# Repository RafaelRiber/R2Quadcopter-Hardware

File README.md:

# R2Quadcopter-Hardware

# Description

The R<sup>2</sup>Quad is an ARM Cortex M0+ Processor-Based radio controlled quadcopter flight controller.

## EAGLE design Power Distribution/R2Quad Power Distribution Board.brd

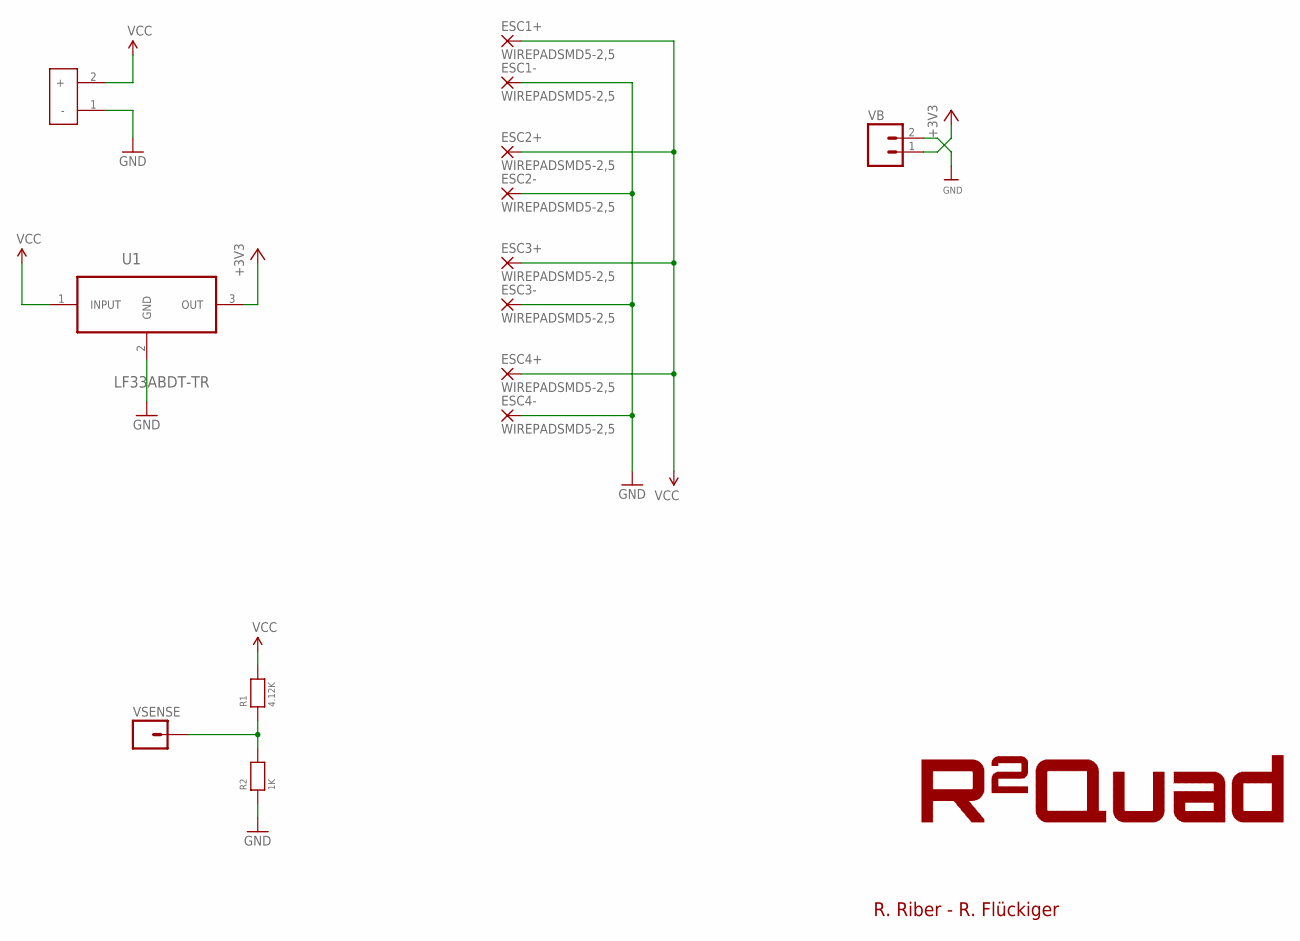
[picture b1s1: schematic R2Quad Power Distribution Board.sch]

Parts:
ESC1+, ESC1-, ESC2+, ESC2-, ESC3+, ESC3-, ESC4+, ESC4-: WIREPADSMD5-2,5; 5-2,5
R1: 4.12K; 0603
R2: 1K; 0603
U1: LF33ABDT-TR; TO228P972X240-3N
U$1: XT60
VB: M02PTH; 1X02
VSENSE: M01PTH; 1X01

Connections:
+3V3: U1.3 (OUT), VB.1
GND: ESC1-.1, ESC2-.1, ESC3-.1, ESC4-.1, R2.1, U1.2 (GND), U$1.1 (-), VB.2
unnamed: R1.1, R2.2, VSENSE.1
VCC: ESC1+.1, ESC2+.1, ESC3+.1, ESC4+.1, R1.2, U1.1 (INPUT), U$1.2 (+)

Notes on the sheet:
R. Riber - R. Flückiger

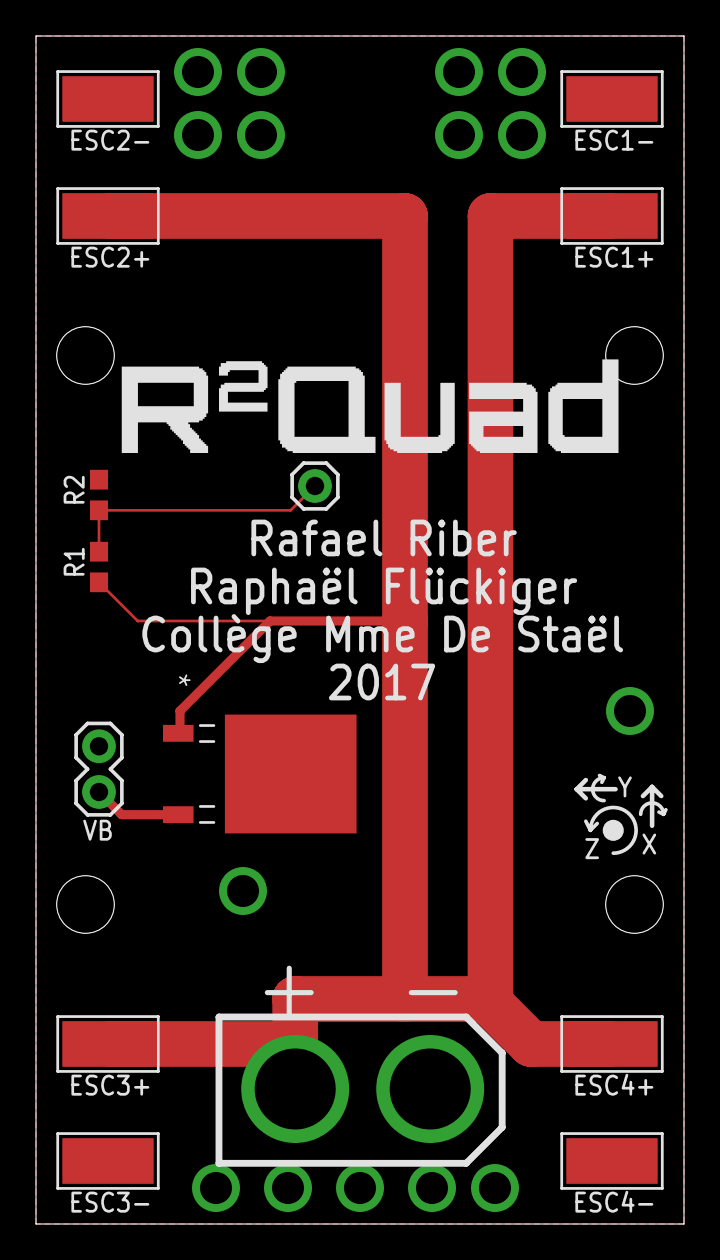
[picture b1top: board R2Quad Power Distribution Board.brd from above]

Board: 2 copper layers, 36.0 x 66.0 mm, 16 parts (0 on the bottom side), 4 nets.

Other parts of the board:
U$2: R2QUAD_LOGO
U$3: SENSOR_AXIS

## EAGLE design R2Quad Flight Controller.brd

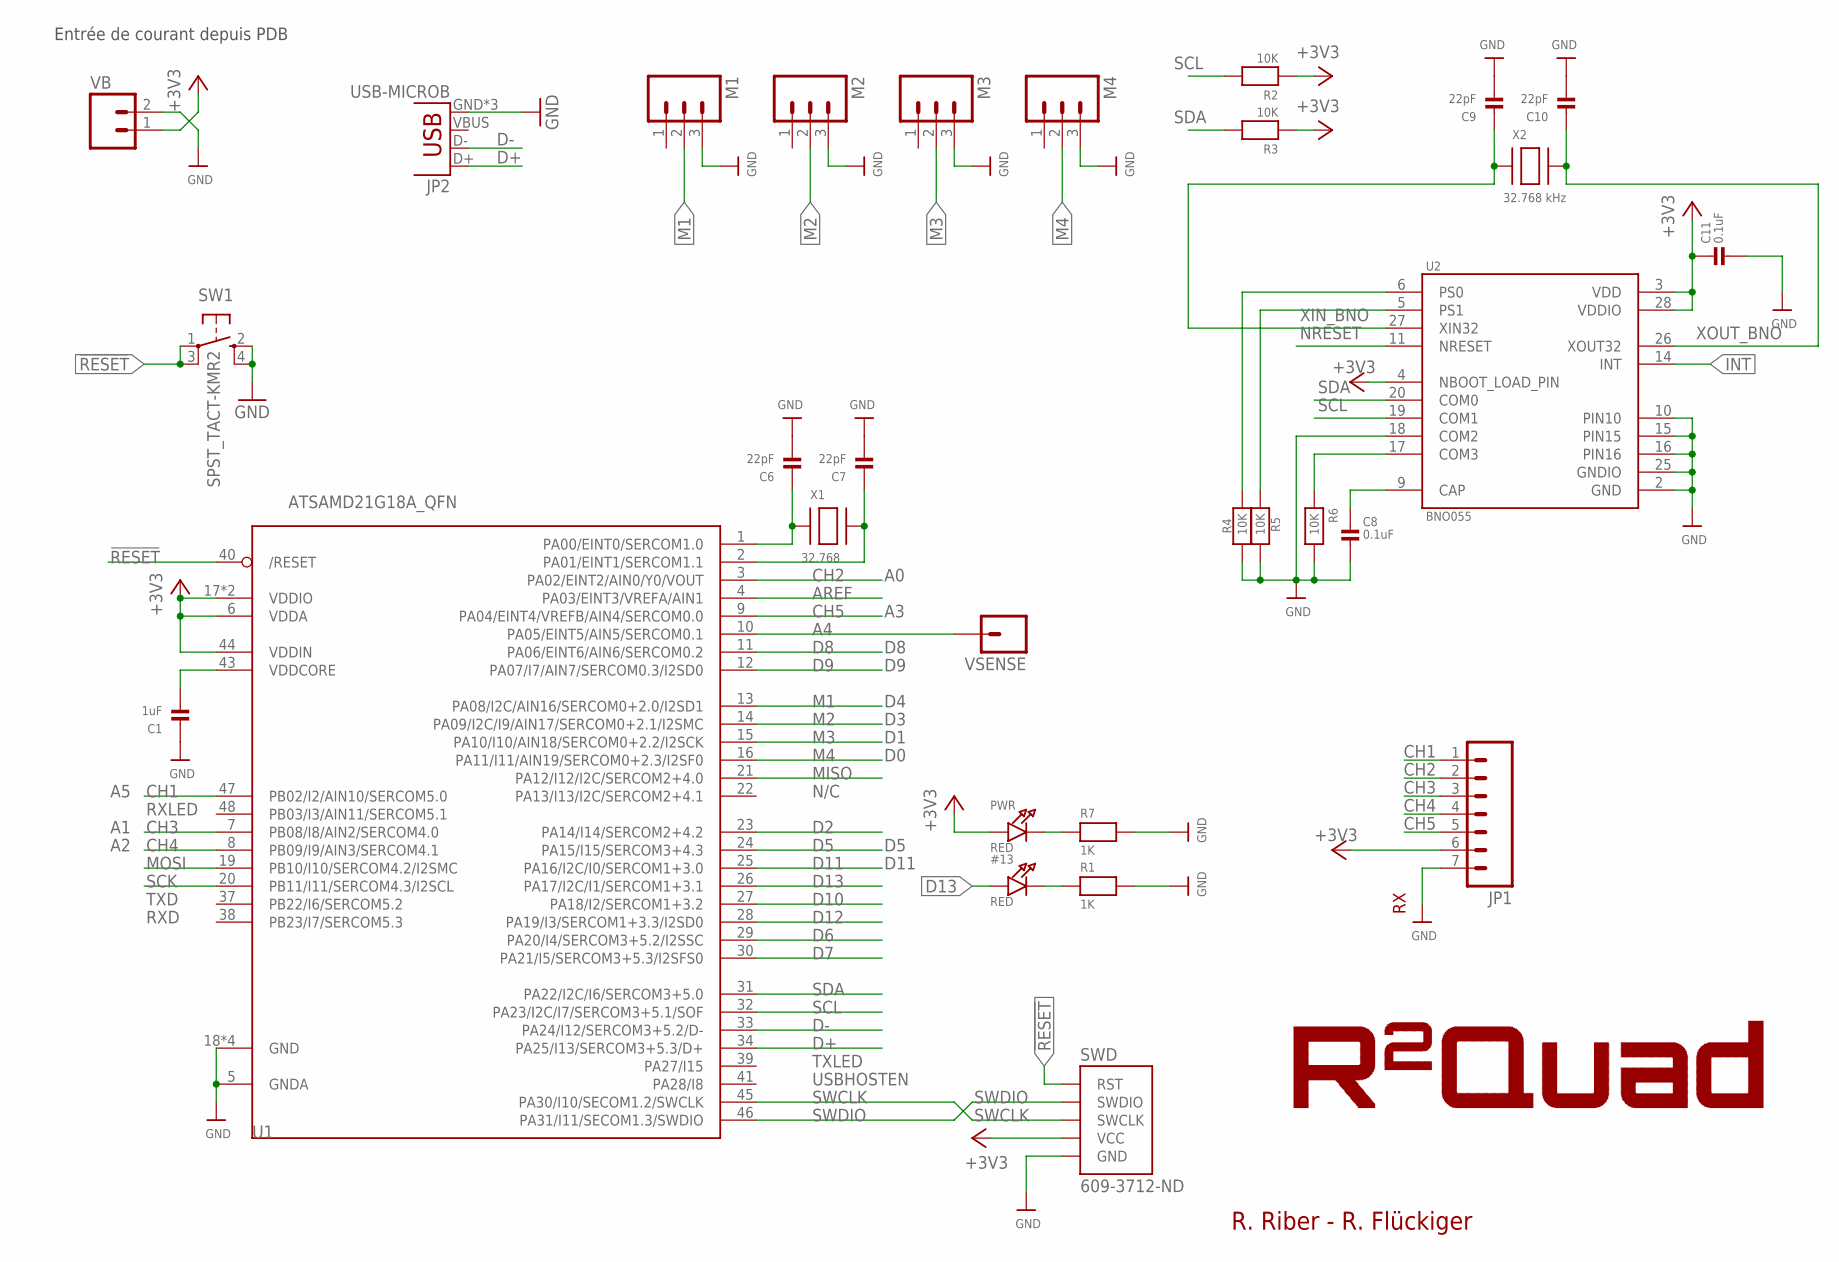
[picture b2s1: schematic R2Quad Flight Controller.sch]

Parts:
#13: RED; CHIPLED_0805; MPN LGQ971
C1: 1uF; 0603
C6, C7, C9, C10: 22pF; 0603
C8, C11: 0.1uF; 0603
JP1: M07; 1X07
JP2: USB-MICROB; MPN 10104110-0001LF
M1, M2, M3, M4: M03PTH; 1X03
PWR: RED; CHIPLED_0805; MPN LGQ971
R1, R7: 1K; 0603; MPN CRCW06032K20JNEA
R2, R3, R4, R5, R6: 10K; 0603; MPN CRCW060310K0FKEA
SW1: SPST_TACT-KMR2; KMR2
SWD: 609-3712-ND; SWD-2X5
U1: ATSAMD21G18A_QFN; TQFN48_7MM
U2: BNO055; LGA28R50P4X10_380X520X100
VB: M02PTH; 1X02
VSENSE: M01PTH; 1X01
X1: 32.768; XTAL3215
X2: 32.768 kHz; XTAL3215

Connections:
!RESET: SW1.1, SW1.3 (P1), SWD.RST, U1.40 (/RESET)
+3V3: C11.2, JP1.6, PWR.A, R2.1, R3.1, SWD.VCC, U1.6 (VDDA), U1.17 (VDDIO), U1.36 (VDDIO), U1.44 (VDDIN), U2.3 (VDD), U2.4 (NBOOT_LOAD_PIN), U2.28 (VDDIO), VB.1
A4: U1.10 (PA05/EINT5/AIN5/SERCOM0.1), VSENSE.1
AREF: U1.4 (PA03/EINT3/VREFA/AIN1)
CH1: JP1.1, U1.47 (PB02/I2/AIN10/SERCOM5.0)
CH2: JP1.2, U1.3 (PA02/EINT2/AIN0/Y0/VOUT)
CH3: JP1.3, U1.7 (PB08/I8/AIN2/SERCOM4.0)
CH4: JP1.4, U1.8 (PB09/I9/AIN3/SERCOM4.1)
CH5: JP1.5, U1.9 (PA04/EINT4/VREFB/AIN4/SERCOM0.0)
D2: U1.23 (PA14/I14/SERCOM2+4.2)
D5: U1.24 (PA15/I15/SERCOM3+4.3)
D6: U1.29 (PA20/I4/SERCOM3+5.2/I2SSC)
D7: U1.30 (PA21/I5/SERCOM3+5.3/I2SFS0)
D8: U1.11 (PA06/EINT6/AIN6/SERCOM0.2)
D9: U1.12 (PA07/I7/AIN7/SERCOM0.3/I2SD0)
D10: U1.27 (PA18/I2/SERCOM1+3.2)
D11: U1.25 (PA16/I2C/I0/SERCOM1+3.0)
D12: U1.28 (PA19/I3/SERCOM1+3.3/I2SD0)
D13: #13.A, U1.26 (PA17/I2C/I1/SERCOM1+3.1)
D+: JP2.D+, U1.34 (PA25/I13/SERCOM3+5.3/D+)
D-: JP2.D-, U1.33 (PA24/I12/SERCOM3+5.2/D-)
GND: C1.1, C6.2, C7.2, C8.1, C9.2, C10.2, C11.1, JP1.7, JP2.GND, JP2.MT1 (GND), JP2.MT2 (GND), M1.3, M2.3, M3.3, M4.3, R1.2, R4.2, R5.2, R6.2, R7.2, SW1.2 (S), SW1.4 (S1), SWD.GND@1 (GND), SWD.GND@2 (GND), SWD.GND@3 (GND), U1.5 (GNDA), U1.18 (GND), U1.35 (GND), U1.42 (GND), U1.THERMAL (GND), U2.2 (GND), U2.10 (PIN10), U2.15 (PIN15), U2.16 (PIN16), U2.18 (COM2), U2.25 (GNDIO), VB.2
INT: U2.14 (INT)
M1: M1.2, U1.13 (PA08/I2C/AIN16/SERCOM0+2.0/I2SD1)
M2: M2.2, U1.14 (PA09/I2C/I9/AIN17/SERCOM0+2.1/I2SMC)
M3: M3.2, U1.15 (PA10/I10/AIN18/SERCOM0+2.2/I2SCK)
M4: M4.2, U1.16 (PA11/I11/AIN19/SERCOM0+2.3/I2SF0)
MISO: U1.21 (PA12/I12/I2C/SERCOM2+4.0)
MOSI: U1.19 (PB10/I10/SERCOM4.2/I2SMC)
unnamed: PWR.C, R7.1
unnamed: C8.2, U2.9 (CAP)
unnamed: R6.1, U2.17 (COM3)
unnamed: R5.1, U2.5 (PS1)
unnamed: R4.1, U2.6 (PS0)
unnamed: C6.1, U1.1 (PA00/EINT0/SERCOM1.0), X1.P$1
unnamed: C7.1, U1.2 (PA01/EINT1/SERCOM1.1), X1.P$2
unnamed: #13.C, R1.1
NRESET: U2.11 (NRESET)
SCK: U1.20 (PB11/I11/SERCOM4.3/I2SCL)
SCL: R2.2, U1.32 (PA23/I2C/I7/SERCOM3+5.1/SOF), U2.19 (COM1)
SDA: R3.2, U1.31 (PA22/I2C/I6/SERCOM3+5.0), U2.20 (COM0)
SWCLK: SWD.SWCLK, U1.45 (PA30/I10/SECOM1.2/SWCLK)
SWDIO: SWD.SWDIO, U1.46 (PA31/I11/SECOM1.3/SWDIO)
VDDCORE1: C1.2, U1.43 (VDDCORE)
XIN_BNO: C9.1, U2.27 (XIN32), X2.P$1
XOUT_BNO: C10.1, U2.26 (XOUT32), X2.P$2

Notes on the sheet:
N/C
TXLED
USBHOSTEN
RXLED
TXD
RXD
D11
R. Riber - R. Flückiger
Entrée de courant depuis PDB

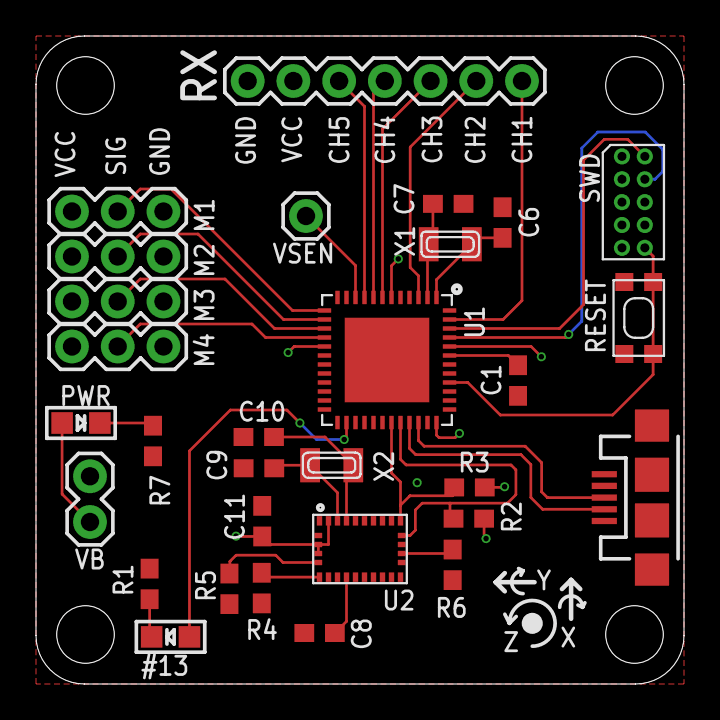
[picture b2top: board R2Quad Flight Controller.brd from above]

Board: 4 copper layers, 36.0 x 36.0 mm, 32 parts (1 on the bottom side), 31 nets.

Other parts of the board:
U$1: R2QUAD_LOGO
U$2: SENSOR_AXIS

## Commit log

2019-12-18 Uploaded Files
2019-12-18 Moved to folder
2019-12-18 Upload Images
2019-12-18 Add images
2019-12-18 Change to png

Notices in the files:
parts and their libraries:
microbuilder: This work is placed in the public domain, and may be freely used for commercial and non-commercial work with the following conditions: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
SparkFun-Connectors: Licensing: Creative Commons ShareAlike 4.0 International - https://creativecommons.org/licenses/by-sa/4.0
